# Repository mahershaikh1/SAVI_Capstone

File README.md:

# SAVI_Capstone
Smartphone Assistant for the Visually Impaired capstone project. Placed 3rd in the Computer and Electrical Engineering Department.

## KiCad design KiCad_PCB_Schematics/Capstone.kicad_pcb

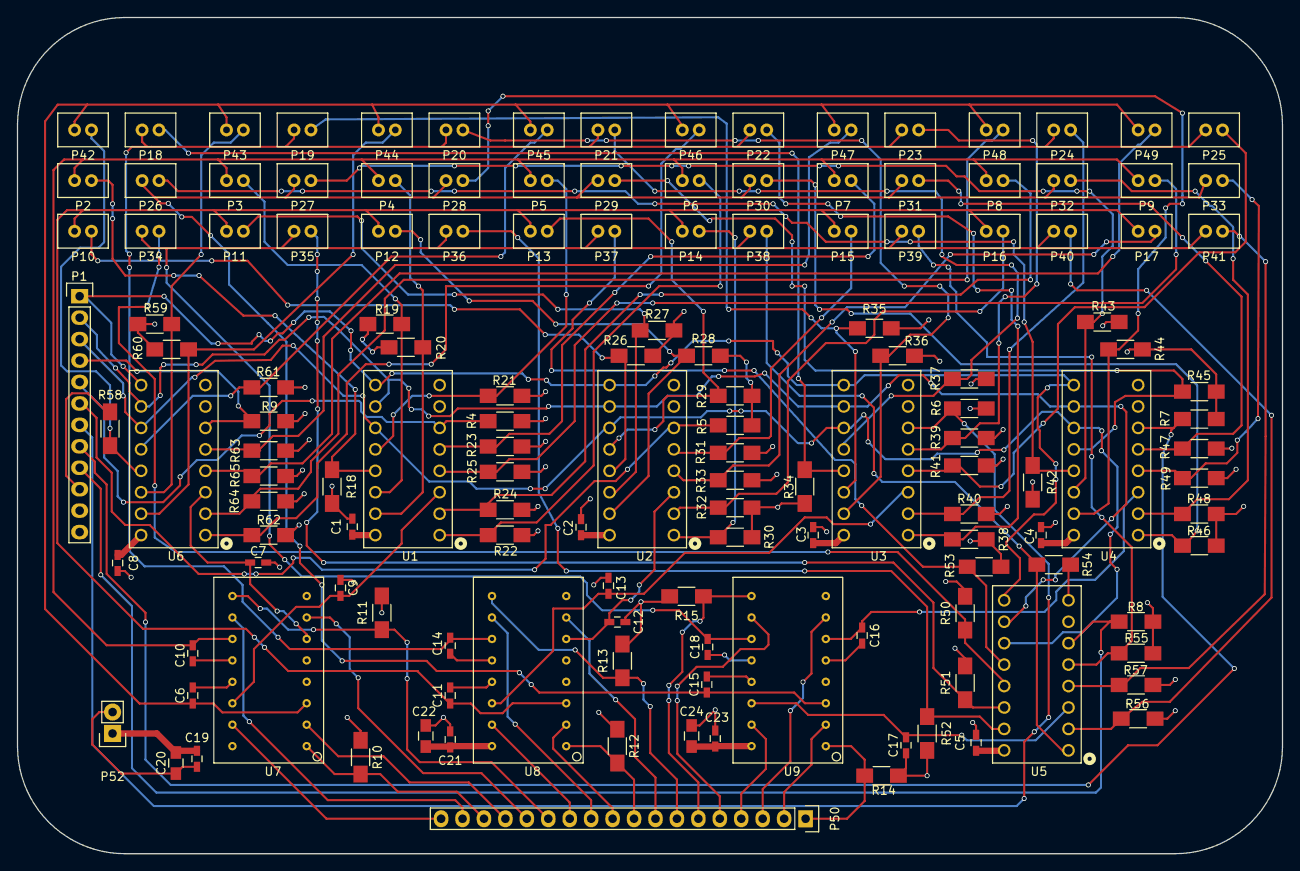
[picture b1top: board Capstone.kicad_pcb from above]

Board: 4 copper layers, 149.9 x 99.1 mm, 144 parts (0 on the bottom side), 89 nets.

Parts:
C1, C2, C3, C4, C5, C8, C19, C23: 0.1uF; C_0603_HandSoldering
C6, C7, C9, C10, C11, C12, C13, C14, C15, C16, C17, C18: 1uF; C_0603_HandSoldering
C20, C22, C24: 10uF; C_0805_HandSoldering
C21: 0.1uf; C_0603_HandSoldering
P1: CONN_01X12; Pin_Header_Straight_1x12
P2: C0_M1; JST_PH
P3: C1_M1; JST_PH
P4: C2_M1; JST_PH
P5: C3_M1; JST_PH
P6: C4_M1; JST_PH
P7: C5_M1; JST_PH
P8: C6_M1; JST_PH
P9: C7_M1; JST_PH
P10: C0_M2; JST_PH
P11: C1_M2; JST_PH
P12: C2_M2; JST_PH
P13: C3_M2; JST_PH
P14: C4_M2; JST_PH
P15: C5_M2; JST_PH
P16: C6_M2; JST_PH
P17: C7_M2; JST_PH
P18: C0_M3; JST_PH
P19: C1_M3; JST_PH
P20: C2_M3; JST_PH
P21: C3_M3; JST_PH
P22: C4_M3; JST_PH
P23: C5_M3; JST_PH
P24: C6_M3; JST_PH
P25: C7_M3; JST_PH
P26: C0_M4; JST_PH
P27: C1_M4; JST_PH
P28: C2_M4; JST_PH
P29: C3_M4; JST_PH
P30: C4_M4; JST_PH
P31: C5_M4; JST_PH
P32: C6_M4; JST_PH
P33: C7_M4; JST_PH
P34: C0_M5; JST_PH
P35: C1_M5; JST_PH
P36: C2_M5; JST_PH
P37: C3_M5; JST_PH
P38: C4_M5; JST_PH
P39: C5_M5; JST_PH
P40: C6_M5; JST_PH
P41: C7_M5; JST_PH
P42: C0_M0; JST_PH
P43: C1_M0; JST_PH
P44: C2_M0; JST_PH
P45: C3_M0; JST_PH
P46: C4_M0; JST_PH
P47: C5_M0; JST_PH
P48: C6_M0; JST_PH
P49: C7_M0; JST_PH
P50: CONN_01X18; Pin_Header_Straight_1x18
P52: CONN_01X02; Pin_Header_Straight_1x02
R4, R5, R6, R7, R8, R9, R10, R11, R12, R13, R14, R15: 4.7k; R_1206_HandSoldering
R18, R19, R20, R21, R22, R23, R24, R25, R26, R27, R28, R29, R30, R31, R32, R33, R34, R35, R36, R37, R38, R39, R40, R41, R42, R43, R44, R45, R46, R47, R48, R49, R50, R51, R52, R53, R54, R55, R56, R57, R58, R59, R60, R61, R62, R63, R64, R65: 10k; R_1206_HandSoldering
U1, U2, U3, U4, U5, U6: MAX4617; 16PDIP_Socket
U7, U8, U9: L293D; L293D_PDIP16

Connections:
/Demux0ToMotor0/C0_M0_V-: P42.2, R58.1, U6.13
/Demux0ToMotor0/C1_M0_V-: P43.2, R59.1, U6.14
/Demux0ToMotor0/C2_M0_V-: P44.2, R60.1, U6.15
/Demux0ToMotor0/C3_M0_V-: P45.2, R61.1, U6.12
/Demux0ToMotor0/C4_M0_V-: P46.2, R62.1, U6.1
/Demux0ToMotor0/C5_M0_V-: P47.2, R63.1, U6.5
/Demux0ToMotor0/C6_M0_V-: P48.2, R64.1, U6.2
/Demux0ToMotor0/C7_M0_V-: P49.2, R65.1, U6.4
/Demux0ToMotor0/M0_V+: C6.1, P42.1, P43.1, P44.1, P45.1, P46.1, P47.1, P48.1, P49.1, U7.3
/Demux0ToMotor0/M0_V-: C7.1, U6.3, U7.6
/Demux1ToMotor1/C0_M1_V-: P2.2, R18.1, U1.13
/Demux1ToMotor1/C1_M1_V-: P3.2, R19.1, U1.14
/Demux1ToMotor1/C2_M1_V-: P4.2, R20.1, U1.15
/Demux1ToMotor1/C3_M1_V-: P5.2, R21.1, U1.12
/Demux1ToMotor1/C4_M1_V-: P6.2, R22.1, U1.1
/Demux1ToMotor1/C5_M1_V-: P7.2, R23.1, U1.5
/Demux1ToMotor1/C6_M1_V-: P8.2, R24.1, U1.2
/Demux1ToMotor1/C7_M1_V-: P9.2, R25.1, U1.4
/Demux1ToMotor1/M1_V+: C10.1, P2.1, P3.1, P4.1, P5.1, P6.1, P7.1, P8.1, P9.1, U7.11
/Demux1ToMotor1/M1_V-: C9.1, U1.3, U7.14
/Demux2ToMotor2/C0_M2_V-: P10.2, R26.1, U2.13
/Demux2ToMotor2/C1_M2_V-: P11.2, R27.1, U2.14
/Demux2ToMotor2/C2_M2_V-: P12.2, R28.1, U2.15
/Demux2ToMotor2/C3_M2_V-: P13.2, R29.1, U2.12
/Demux2ToMotor2/C4_M2_V-: P14.2, R30.1, U2.1
/Demux2ToMotor2/C5_M2_V-: P15.2, R31.1, U2.5
/Demux2ToMotor2/C6_M2_V-: P16.2, R32.1, U2.2
/Demux2ToMotor2/C7_M2_V-: P17.2, R33.1, U2.4
/Demux2ToMotor2/M2_V+: C11.1, P10.1, P11.1, P12.1, P13.1, P14.1, P15.1, P16.1, P17.1, U8.3
/Demux2ToMotor2/M2_V-: C12.1, U2.3, U8.6
/Demux3ToMotor3/C0_M3_V-: P18.2, R34.1, U3.13
/Demux3ToMotor3/C1_M3_V-: P19.2, R35.1, U3.14
/Demux3ToMotor3/C2_M3_V-: P20.2, R36.1, U3.15
/Demux3ToMotor3/C3_M3_V-: P21.2, R37.1, U3.12
/Demux3ToMotor3/C4_M3_V-: P22.2, R38.1, U3.1
/Demux3ToMotor3/C5_M3_V-: P23.2, R39.1, U3.5
/Demux3ToMotor3/C6_M3_V-: P24.2, R40.1, U3.2
/Demux3ToMotor3/C7_M3_V-: P25.2, R41.1, U3.4
/Demux3ToMotor3/M3_V+: C14.1, P18.1, P19.1, P20.1, P21.1, P22.1, P23.1, P24.1, P25.1, U8.11
/Demux3ToMotor3/M3_V-: C13.1, U3.3, U8.14
/Demux4ToMotor4/C0_M4_V-: P26.2, R42.1, U4.13
/Demux4ToMotor4/C1_M4_V-: P27.2, R43.1, U4.14
/Demux4ToMotor4/C2_M4_V-: P28.2, R44.1, U4.15
/Demux4ToMotor4/C3_M4_V-: P29.2, R45.1, U4.12
/Demux4ToMotor4/C4_M4_V-: P30.2, R46.1, U4.1
/Demux4ToMotor4/C5_M4_V-: P31.2, R47.1, U4.5
/Demux4ToMotor4/C6_M4_V-: P32.2, R48.1, U4.2
/Demux4ToMotor4/C7_M4_V-: P33.2, R49.1, U4.4
/Demux4ToMotor4/M4_V+: C15.1, P26.1, P27.1, P28.1, P29.1, P30.1, P31.1, P32.1, P33.1, U9.3
/Demux4ToMotor4/M4_V-: C16.1, U4.3, U9.6
/Demux5ToMotor5/C0_M5_V-: P34.2, R50.1, U5.13
/Demux5ToMotor5/C1_M5_V-: P35.2, R51.1, U5.14
/Demux5ToMotor5/C2_M5_V-: P36.2, R52.1, U5.15
/Demux5ToMotor5/C3_M5_V-: P37.2, R53.1, U5.12
/Demux5ToMotor5/C4_M5_V-: P38.2, R54.1, U5.1
/Demux5ToMotor5/C5_M5_V-: P39.2, R55.1, U5.5
/Demux5ToMotor5/C6_M5_V-: P40.2, R56.1, U5.2
/Demux5ToMotor5/C7_M5_V-: P41.2, R57.1, U5.4
/Demux5ToMotor5/M5_V+: C18.1, P34.1, P35.1, P36.1, P37.1, P38.1, P39.1, P40.1, P41.1, U9.11
/Demux5ToMotor5/M5_V-: C17.1, U5.3, U9.14
CONTROL_A: P1.3, U1.11, U2.11, U3.11, U4.11, U5.11, U6.11
CONTROL_B: P1.2, U1.10, U2.10, U3.10, U4.10, U5.10, U6.10
CONTROL_C: P1.1, U1.9, U2.9, U3.9, U4.9, U5.9, U6.9
ENABLE_H0: P50.16, R10.1, U7.1
ENABLE_H1: P50.13, R11.1, U7.9
ENABLE_H2: P50.9, R12.1, U8.1
ENABLE_H3: P50.7, R13.1, U8.9
ENABLE_H4: P50.1, R14.1, U9.1
ENABLE_H5: P50.6, R15.1, U9.9
ENABLE_M0: P1.4, R9.1, U6.6
ENABLE_M1: P1.5, R4.1, U1.6
ENABLE_M2: P1.6, R5.1, U2.6
ENABLE_M3: P1.7, R6.1, U3.6
ENABLE_M4: P1.8, R7.1, U4.6
ENABLE_M5: P1.9, R8.1, U5.6
GND: C1.2, C2.2, C3.2, C4.2, C5.2, C6.2, C7.2, C8.2, C9.2, C10.2, C11.2, C12.2, C13.2, C14.2, C15.2, C16.2, C17.2, C18.2, C19.2, C20.2, C21.2, C22.2, C23.2, C24.2, P1.10, P1.11, P1.12, P52.2, R4.2, R5.2, R6.2, R7.2, R8.2, R9.2, R10.2, R11.2, R12.2, R13.2, R14.2, R15.2, R18.2, R19.2, R20.2, R21.2, R22.2, R23.2, R24.2, R25.2, R26.2, R27.2, R28.2, R29.2, R30.2, R31.2, R32.2, R33.2, R34.2, R35.2, R36.2, R37.2, R38.2, R39.2, R40.2, R41.2, R42.2, R43.2, R44.2, R45.2, R46.2, R47.2, R48.2, R49.2, R50.2, R51.2, R52.2, R53.2, R54.2, R55.2, R56.2, R57.2, R58.2, R59.2, R60.2, R61.2, R62.2, R63.2, R64.2, R65.2, U1.8, U2.8, U3.8, U4.8, U5.8, U6.8, U7.4, U7.5, U7.12, U7.13, U8.4, U8.5, U8.12, U8.13, U9.4, U9.5, U9.12, U9.13
M0_S1: P50.15, U7.2
M0_S2: P50.14, U7.7
M1_S1: P50.17, U7.10
M1_S2: P50.18, U7.15
M2_S1: P50.10, U8.2
M2_S2: P50.8, U8.7
M3_S1: P50.11, U8.10
M3_S2: P50.12, U8.15
M4_S1: P50.2, U9.2
M4_S2: P50.3, U9.7
M5_S1: P50.5, U9.10
M5_S2: P50.4, U9.15
Vcc: C1.1, C2.1, C3.1, C4.1, C5.1, C8.1, C19.1, C20.1, C21.1, C22.1, C23.1, C24.1, P52.1, U1.16, U2.16, U3.16, U4.16, U5.16, U6.16, U7.8, U7.16, U8.8, U8.16, U9.8, U9.16

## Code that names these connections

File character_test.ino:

#define output(PIN) pinMode((PIN), OUTPUT)
#define input(PIN) pinMode((PIN), INPUT)
#define analog(PIN, VALUE) pinMode((PIN), OUTPUT); analogWrite((PIN), (VALUE))

#define CONTROL_A 47
#define CONTROL_B 46
#define CONTROL_C 45
#define DEMUX_0 48
#define DEMUX_1 49
#define DEMUX_2 50
#define DEMUX_3 51
#define DEMUX_4 52
#define DEMUX_5 53

#define ENABLE_H0 7
#define ENABLE_H1 6
#define ENABLE_H2 5
#define ENABLE_H3 4
#define ENABLE_H4 3
#define ENABLE_H5 2
#define M0_S1 22
#define M0_S2 23
#define M1_S1 24
#define M1_S2 25
#define M2_S1 26
#define M2_S2 27
#define M3_S1 28
#define M3_S2 29
#define M4_S1 30
#define M4_S2 31
#define M5_S1 32
#define M5_S2 33

void setup() {
  // set up all pins as output
  output(CONTROL_A); //control A
  output(CONTROL_B); //control B
  output(CONTROL_C); //control C
  output(DEMUX_0); //enable demux0
  output(DEMUX_1); //enable demux1
  output(DEMUX_2); //enable demux2
  output(DEMUX_3); //enable demux3
  output(DEMUX_4); //enable demux4
  output(DEMUX_5); //enable demux5

  output(ENABLE_H0);
  output(ENABLE_H1);
  output(ENABLE_H2);
  output(ENABLE_H3);
  output(ENABLE_H4);
  output(ENABLE_H5);
  output(M0_S1);
  output(M0_S2);
  output(M1_S1);
  output(M1_S2);
  output(M2_S1);
  output(M2_S2);
  output(M3_S1);
  output(M3_S2);
  output(M4_S1);
  output(M4_S2);
  output(M5_S1);
  output(M5_S2);

  double percent = 1;
  int value = percent * 255;

  analog(ENABLE_H0, value);
  analog(ENABLE_H1, value);
  analog(ENABLE_H2, value);
  analog(ENABLE_H3, value);
  analog(ENABLE_H4, value);
  analog(ENABLE_H5, value);
  
  digitalWrite(DEMUX_0, LOW);
  digitalWrite(DEMUX_1, LOW);
  digitalWrite(DEMUX_2, LOW);
  digitalWrite(DEMUX_3, LOW);
  digitalWrite(DEMUX_4, LOW);
  digitalWrite(DEMUX_5, LOW);
  
  Serial.println("Not dead");
}

void loop() {
  selectCharacter(1);
  //for (int k = 0; k < 8; ++k) {
    //selectCharacter(k);
    for (int i = 0; i < 6; ++i) {
      for (int j = 0; j < 5; ++j) {
        setMotor(i, false, true);
        delay(25);
        setMotor(i, false, false);
        delay(1000);
        setMotor(i, true, false);
        delay(25);
        setMotor(i, false, false);
        delay(1000);
      }
    }
  //}
}

void selectCharacter(int character) {
  digitalWrite(CONTROL_A, character & 1 ^ LOW);
  digitalWrite(CONTROL_B, character & 2 ^ LOW);
  digitalWrite(CONTROL_C, character & 4 ^ LOW);
}

void setMotor(int pin, bool currentState, bool nextState) {
  // TODO validate this against hardware
  if (currentState == nextState) {
    digitalWrite(getFirstPin(pin), LOW);
    digitalWrite(getSecondPin(pin), LOW);
  }
  else if (currentState) {
    // currentState is UP, nextState is DOWN
    digitalWrite(getFirstPin(pin), HIGH);
    digitalWrite(getSecondPin(pin), LOW);
  }
  else {
    digitalWrite(getFirstPin(pin), LOW);
    digitalWrite(getSecondPin(pin), HIGH);
  }
}

int getFirstPin(int pin) {
  switch(pin) {
    case 0:
      return M0_S1;
    case 1:
      return M1_S1;
    case 2:
      return M2_S1;
    case 3:
      return M3_S1;
    case 4:
      return M4_S1;
    case 5:
      return M5_S1;
  }
}

int getSecondPin(int pin) {
  switch(pin) {
    case 0:
      return M0_S2;
    case 1:
      return M1_S2;
    case 2:
      return M2_S2;
    case 3:
      return M3_S2;
    case 4:
      return M4_S2;
    case 5:
      return M5_S2;
  }
}

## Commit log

2018-03-02 Add files via upload
    SolidWorks Files
2018-03-02 Add files via upload
    Project Report
2018-03-02 Add files via upload
    Device case SolidWorks files
2018-03-02 Add files via upload
    All files related to PCB
2018-03-02 Add files via upload
    Video clips of pin mechanism moving
2018-03-02 Add files via upload
    Screenshot of PCB. Designed in KiCad
2018-03-02 Add files via upload
    Arduino code
